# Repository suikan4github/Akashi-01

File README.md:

# Akashi-01
A Test jig board for the Murasaki library. Testing I2C, SPI, and UART on the Nucleo 64. This project is for Murasaki development. Not for the Murasaki application developer. 

## Functionality
This board is designed to test the serial port's functionality of the STM32 series MCU. The connectors can be directly mounted on the Nucleo 64 series board. With this board, the following can be tested :
- Serial Port TX and RX. With/without hardware handshake.
- I2C port Master and Slave. 
- SPI port Master and Slave. 

All above are achieved by connecting peripheral port head-to-head ( Serial port is an exception. It just tied TX to RX and RTS to CTS respectively). In addition to these test feature, additional parts can be mount : 
- Serial 7 segments LED display by Spark fun. 
- Rotary encoder with a switch to test the encoder functionality of timer and EXTI (External Interrupt of the STM32 MCU). 

## Development
- [KiCad 5.1](http://kicad-pcb.org/blog/2019/03/KiCad-5.1.0-Release/)
- [Nucleo F091RC](https://www.st.com/ja/evaluation-tools/nucleo-f091rc.html)
- [Nucleo L152RE](https://www.st.com/ja/evaluation-tools/nucleo-l152re.html)
- [Nucleo F446RE](https://www.st.com/ja/evaluation-tools/nucleo-f446re.html)

The schematics [can be downloaded](docs/Akashi-01.pdf) as PDF format. 

## Usage
The test program works with this board will be published as [murasaki_test_fundamental](https://github.com/suikan4github/murasaki_test_foundemental) project in future. 

If you develop a software works with this board, that software has to follow the pin configuration below. Note that the master-slave configuration is critical. If wrong, the MCU may be broken. 

I2C2_SDA is PB11 for both Nucleo L152RE and F091RC. But it is PC12 for the Nucleo F446RE.

**CAUTION** : Nucleo F446 CN10 pin 18 have to be cut. This pin is connected to VCAP1 pin of the STM32F446 internally. The VCAP1 is not for the peripheral usage. Thus, cutting pin 18 is not problem.

## License
This PCB design is released under the [Creative Commons Attribution 4.0 International license](https://creativecommons.org/licenses/by/4.0/). You are welcome to use this design for commercial purposes.

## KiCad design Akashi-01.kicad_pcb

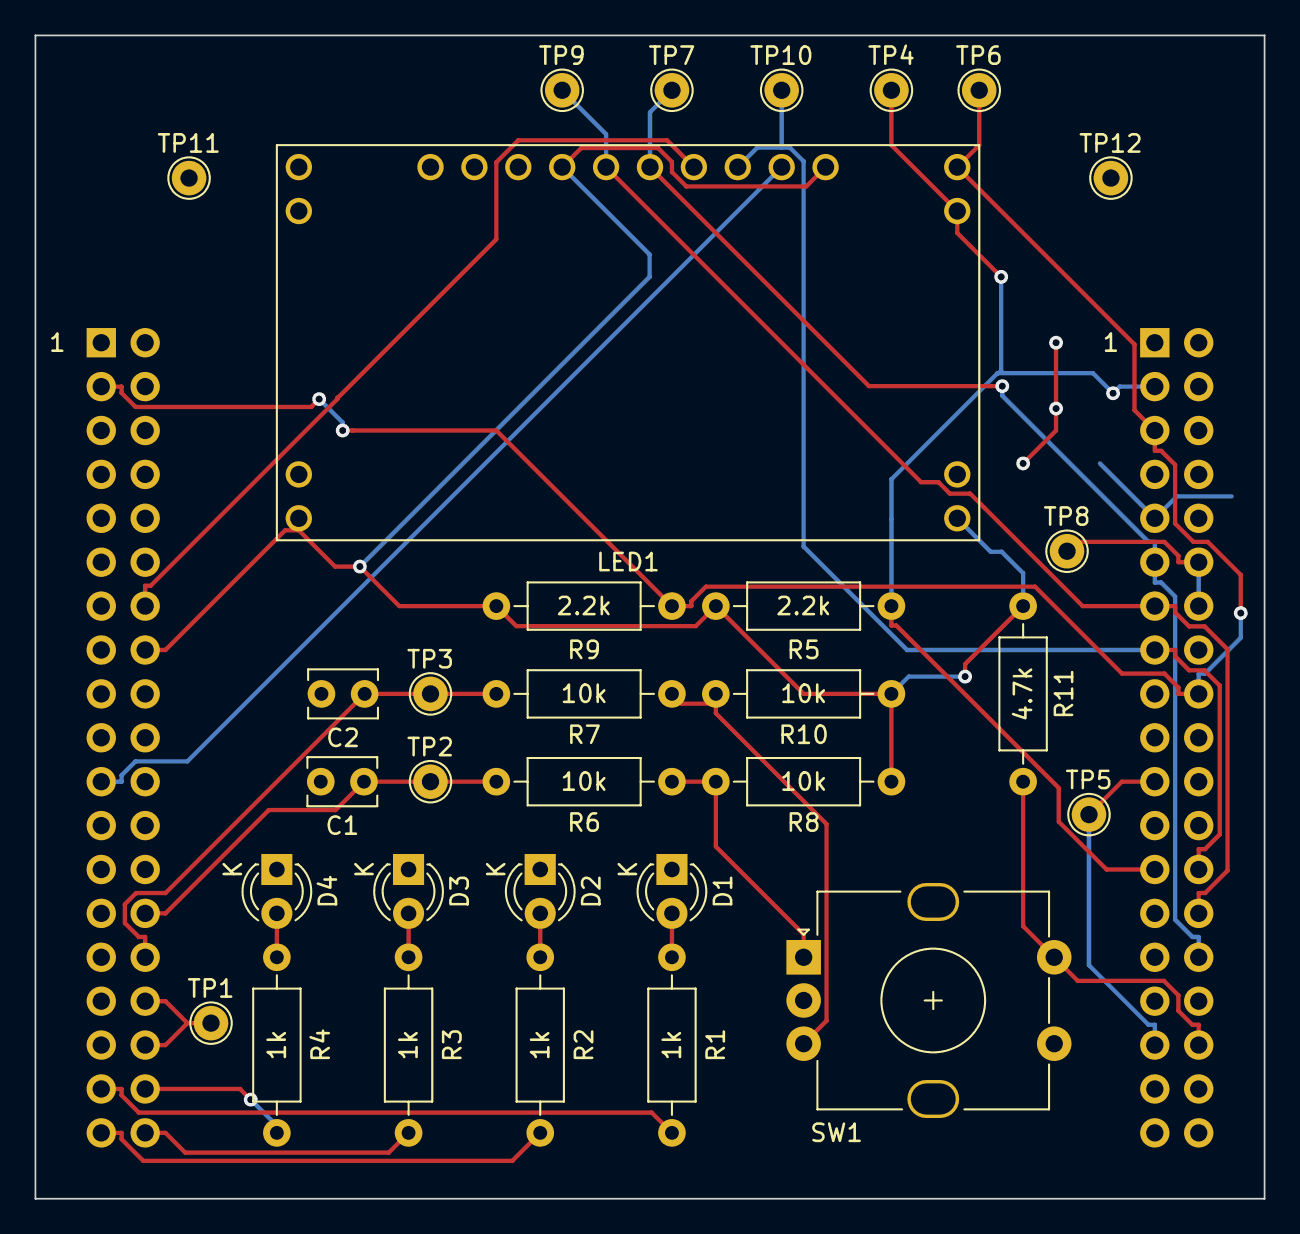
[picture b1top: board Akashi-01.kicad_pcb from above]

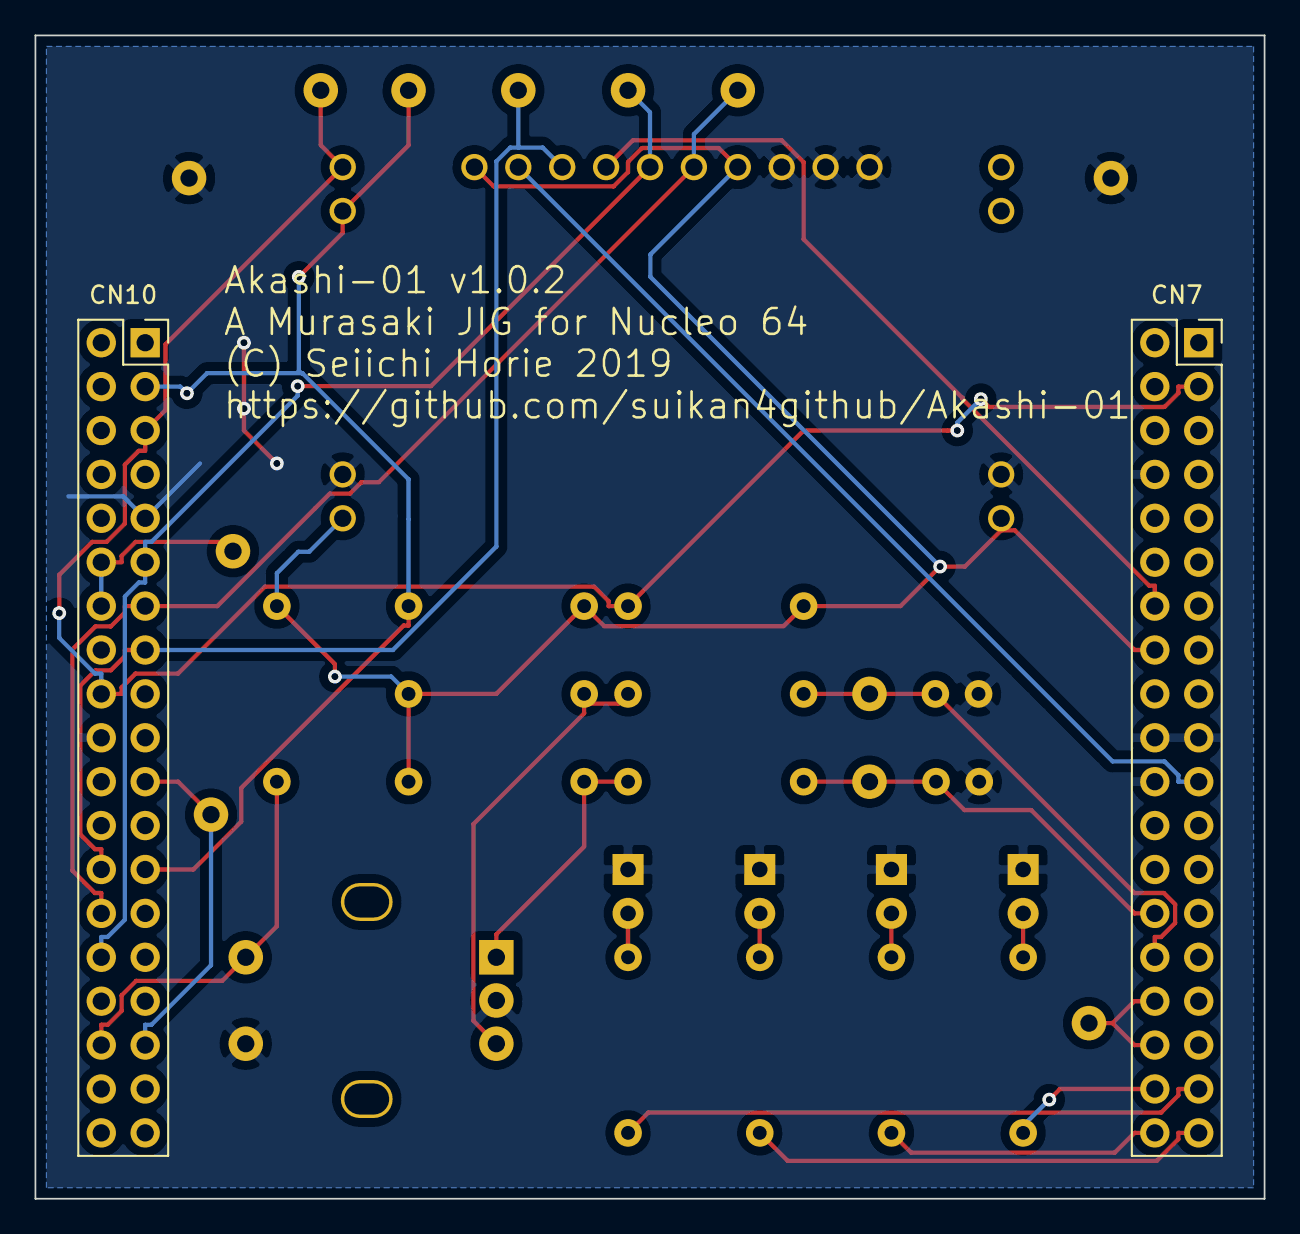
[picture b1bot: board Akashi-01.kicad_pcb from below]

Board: 2 copper layers, 71.1 x 67.3 mm, 33 parts (2 on the bottom side), 25 nets.

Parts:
C1, C2: 0.01u; C_Disc_D3.8mm_W2.6mm_P2.50mm
CN7, CN10: PPPC192LFBN-RC; PinSocket_2x19_P2.54mm_Vertical
D1, D2, D3, D4: LED; LED_D3.0mm_Clear
LED1: SparkFun-7-Segment-Serial-Display-Red; SparkFun-7-Segment-Serial-Display
R1, R2, R3, R4: 1k; R_Axial_DIN0207_L6.3mm_D2.5mm_P10.16mm_Horizontal
R5, R9: 2.2k; R_Axial_DIN0207_L6.3mm_D2.5mm_P10.16mm_Horizontal
R6, R7, R8, R10: 10k; R_Axial_DIN0207_L6.3mm_D2.5mm_P10.16mm_Horizontal
R11: 4.7k; R_Axial_DIN0207_L6.3mm_D2.5mm_P10.16mm_Horizontal
SW1: PEC11R-4220F-S0024; RotaryEncoder_Alps_EC12E-Switch_Vertical_H20mm_CircularMoun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
TP1: nSS; TestPoint_THTPad_D2.0mm_Drill1.0mm
TP2: CH1; TestPoint_THTPad_D2.0mm_Drill1.0mm
TP3: CH2; TestPoint_THTPad_D2.0mm_Drill1.0mm
TP4: SCL; TestPoint_THTPad_D2.0mm_Drill1.0mm
TP5: TX; TestPoint_THTPad_D2.0mm_Drill1.0mm
TP6: SDA; TestPoint_THTPad_D2.0mm_Drill1.0mm
TP7: SCK; TestPoint_THTPad_D2.0mm_Drill1.0mm
TP8: RTS; TestPoint_THTPad_D2.0mm_Drill1.0mm
TP9: MISO; TestPoint_THTPad_D2.0mm_Drill1.0mm
TP10: MOSI; TestPoint_THTPad_D2.0mm_Drill1.0mm
TP11, TP12: GND; TestPoint_THTPad_D2.0mm_Drill1.0mm

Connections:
+3V3: CN7.16, LED1.4, LED1.5, LED1.9, LED1.15, R5.1, R8.1, R9.1, R10.1, R11.1
/I2C1_SCL: CN10.3, CN10.25, LED1.7, R5.2, TP4.1
/I2C1_SDA: CN7.3, CN10.5, CN10.18, LED1.8, R9.2, TP6.1
/LED1: CN7.35, R1.1
/LED2: CN7.37, R2.1
/LED3: CN7.38, R3.1
/LED4: CN7.36, R4.1
/SPI1_MISO: CN10.13, CN10.28, LED1.14, TP9.1
/SPI1_MOSI: CN10.15, CN10.26, LED1.11, TP10.1
/SPI1_NSS: CN7.32, CN7.34, TP1.1
/SPI1_SCK: CN10.11, CN10.30, LED1.13, TP7.1
/SW1: CN10.34, R11.2, SW1.S1
/TIM2_CH1: C1.1, CN7.28, R6.2, TP2.1
/TIM2_CH2: C2.1, CN7.30, R7.2, TP3.1
/UART1_TX: CN10.21, CN10.33, TP5.1
/USART1_CTS: CN10.12, CN10.14, TP8.1
/nLEDCS: CN7.21, LED1.10
/nRESET: CN7.14, LED1.12
GND: C1.2, C2.2, CN7.8, CN7.19, CN7.20, CN7.22, CN10.9, CN10.20, D1.1, D2.1, D3.1, D4.1, LED1.3, LED1.6, LED1.16, LED1.17, LED1.18, SW1.C, SW1.S2, TP11.1, TP12.1
unnamed: D1.2, R1.2
unnamed: D2.2, R2.2
unnamed: D3.2, R3.2
unnamed: D4.2, R4.2
unnamed: R6.1, R8.2, SW1.A
unnamed: R7.1, R10.2, SW1.B

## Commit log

2019-03-28 Moved from the old project
2019-03-31 Gerber generated.
    The gerber was sent to fab Mar/31/2019.
    Added schematics and README.md
2019-03-31 Prepare to publish
2019-04-14 Change the copy right size.
    From 1.0 to 1.5
    Issue : Copyright is too small #2
    https://github.com/suikan4github/Akashi-01/issues/2
2019-04-14 Record the CHANGELOG
2019-04-14 Change test point drill size.
    Issue 1 : Test point hole is too small #1
    https://github.com/suikan4github/Akashi-01/issues/1
2019-04-14 Record CHANGELOG.md
2019-04-14 Change footprint
    Issue 3 : Update frootprint of the serial display #3
    https://github.com/suikan4github/Akashi-01/issues/3
2019-04-14 Generate gerber
2019-05-12 Serial LED has been fixed.
    Issue : Serial 7 segment module has wrong pin assigment. #3
    https://github.com/suikan4github/Suikan-KiCad-Libraries/issues/3
2019-05-12 Update CHANGELOG
    Issue : schematic with wrong pin assign Serial 7 segment display. #4
    https://github.com/suikan4github/Akashi-01/issues/4
2019-05-12 Fixed CHANGELOG
2019-05-12 Update schematic
2019-11-04 Fixed comment on the Schematics and README
2019-12-30 Library structure changed.
    Issue #5 : Make thirdparty library access to internal
    https://github.com/suikan4github/Akashi-01/issues/5
2020-01-03 Cache updated
2020-01-03 Modify the mistaken connection of SCL/SDA to LED module.
    LED1 module SCL/SDA is connected reverse. #7
    https://github.com/suikan4github/Akashi-01/issues/7
2020-01-03 Change the SW1 mount hole.
    Issue 8 : SW1 mount point hall is too small
    https://github.com/suikan4github/Akashi-01/issues/8
2020-01-03 Added CN10 Pin 18 note to readme.
    Issue 9 : Need description of the CN10 pin 18
    https://github.com/suikan4github/Akashi-01/issues/9
2020-01-04 Silk updated.
    Issue 11 : The Silk have to be updated
    https://github.com/suikan4github/Akashi-01/issues/11
